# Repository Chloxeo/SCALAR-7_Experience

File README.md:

# SCALAR-7 : Carte Experience Bas

Experiment board of the **lower stage** of **SCALAR-7**, a two-stage rocket launched at **C'Space 2026**.
It measures the stage's flight parameters (accelerations, angular rates, attitude, pressure, altitude, temperature), tracks its position with GNSS, controls two onboard cameras and downlinks its data to the ground over LoRa.

---
## Table of contents

- [Board features](#board-features)
- [Architecture](#architecture)
  - [Power supply](#power-supply)
  - [Microcontroller](#microcontroller)
  - [Telemetry](#telemetry)
  - [Experiments](#experiments)
  - [HMI connection](#hmi-connection)
- [Main components](#main-components)
- [Repository structure](#repository-structure)

---

## Board features

| Function | Implementation |
|---|---|
| Processing / logging | Raspberry Pi **Pico** (RP2040) |
| Flight measurements | **WitMotion WT901B** inertial measurement unit: accelerometer, gyroscope, magnetometer, barometer, temperature (UART, I²C optional) |
| Positioning | **u-blox MAX-M10S** GNSS module (I²C, UART optional) |
| Ground link | **Microchip RN2483** LoRa 868 MHz module (UART), RF output split across two antennas |
| Video | Two JST connectors for the cameras (power, UART, control GPIOs) |
| Power supply | 2S battery, protected input (reverse polarity, overcurrent), 3.3 V and 5 V regulators |
| HMI interface | D-Sub 15 connector: power, jack, status LED, debug UART and SWD, camera control |
| Indicators | Power LED, GNSS PPS LED |

---

## Architecture

```mermaid
flowchart LR
    BAT[2S battery<br/>J5] --> IHM[HMI connector<br/>D-Sub 15]
    IHM -- VBATT_IHM --> PROT[Reverse-polarity P-MOS<br/>+ polyfuse]
    PROT --> REG33[LD1117 3V3]
    PROT --> REG5[L7805 5V]
    PROT --> CAM[Cameras 1 and 2]

    REG5 --> PICO[Raspberry Pi Pico]
    IHM -- ALIM_DEBUG --> PICO
    REG33 --> GPS[MAX-M10S<br/>GNSS]
    REG33 --> LORA[RN2483<br/>LoRa 868 MHz]
    REG5 --> IMU[WT901B<br/>IMU + barometer]

    GPS <-- I2C --> PICO
    LORA <-- UART --> PICO
    IMU <-- UART --> PICO
    CAM <-- UART / GPIO --> PICO
    LORA --> SPLIT[Power divider] --> ANT[2 antennas]
    IHM <-- UART / SWD / jack --> PICO
```

### Power supply

The board is powered by a **2S** battery. The supply goes through the HMI before coming back to the board, so the board can be switched on from the outside. The input is protected against reverse polarity (P-MOSFET) and overcurrent (polyfuse), then two linear regulators generate the **3V3** rail (GNSS, LoRa) and the **5V** rail (Pico, IMU). The cameras are powered directly from the protected battery line.

### Microcontroller

A **Raspberry Pi Pico** handles IMU and GNSS acquisition, camera control and LoRa frame transmission. It is mounted on two pin headers that also serve as test points. Its VSYS input is supplied either by the board's 5V rail or by the HMI debug supply through two diodes, so it can be programmed without the battery.

### Telemetry

- **GNSS**: a **u-blox MAX-M10S** module provides the position and a PPS signal. It connects to an external antenna and keeps its data in memory thanks to a backup battery.
- **LoRa**: an **RN2483** module (868 MHz, UART) sends the data to the ground. Its RF output is split across two antennas by a power divider.

### Experiments

- **Flight measurements**: **WT901B** inertial measurement unit, connected over UART. It provides accelerations, angular rates, attitude, pressure, altitude and temperature.
- **Video**: two cameras, powered by the board and controlled over UART and GPIO.

### HMI connection

The **D-Sub 15** connector links the board to the HMI. It carries the battery supply (out and back, for switching the board on), the jack, the status LED, the Pico's debug UART and SWD, and the camera control GPIOs.

---

## Main components

| Ref. | Component | Function |
|---|---|---|
| — | Raspberry Pi Pico | Microcontroller |
| U1 | u-blox MAX-M10S | GNSS receiver |
| U2 | Microchip RN2483 | LoRa 868 MHz module |
| U3 | PD0810J5050S2HF | RF power divider |
| W1 | WitMotion WT901B | IMU with barometer |
| IC2 | ST LD1117DT33TR | 3.3 V regulator |
| IC3 | ST L7805CDT-TR | 5 V regulator |
| Q2 | Vishay SQD50P04-13L | Reverse-polarity protection |
| F1 | Littelfuse 1812L260/16MR | Polyfuse |
| J2 | D-Sub 15 | HMI connection |
| J8, J9 | 5-pin connectors | Cameras |

---

## Repository structure

```
SCALAR-7_Carte_Experience_Bas/
├── hardware/          # KiCad project
├── images/
├── schematic.pdf
└── README.md
```

---

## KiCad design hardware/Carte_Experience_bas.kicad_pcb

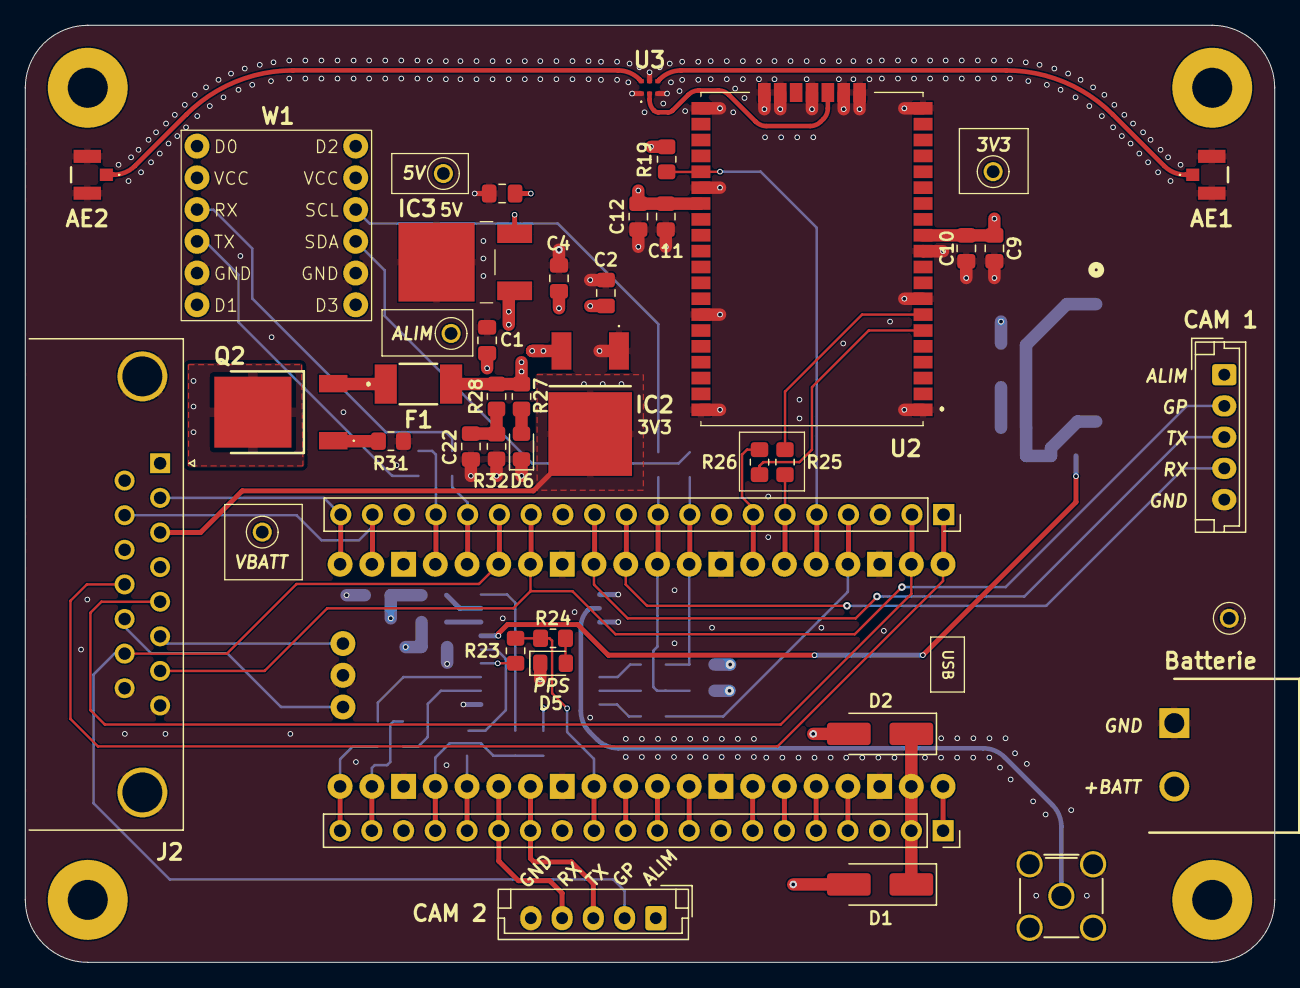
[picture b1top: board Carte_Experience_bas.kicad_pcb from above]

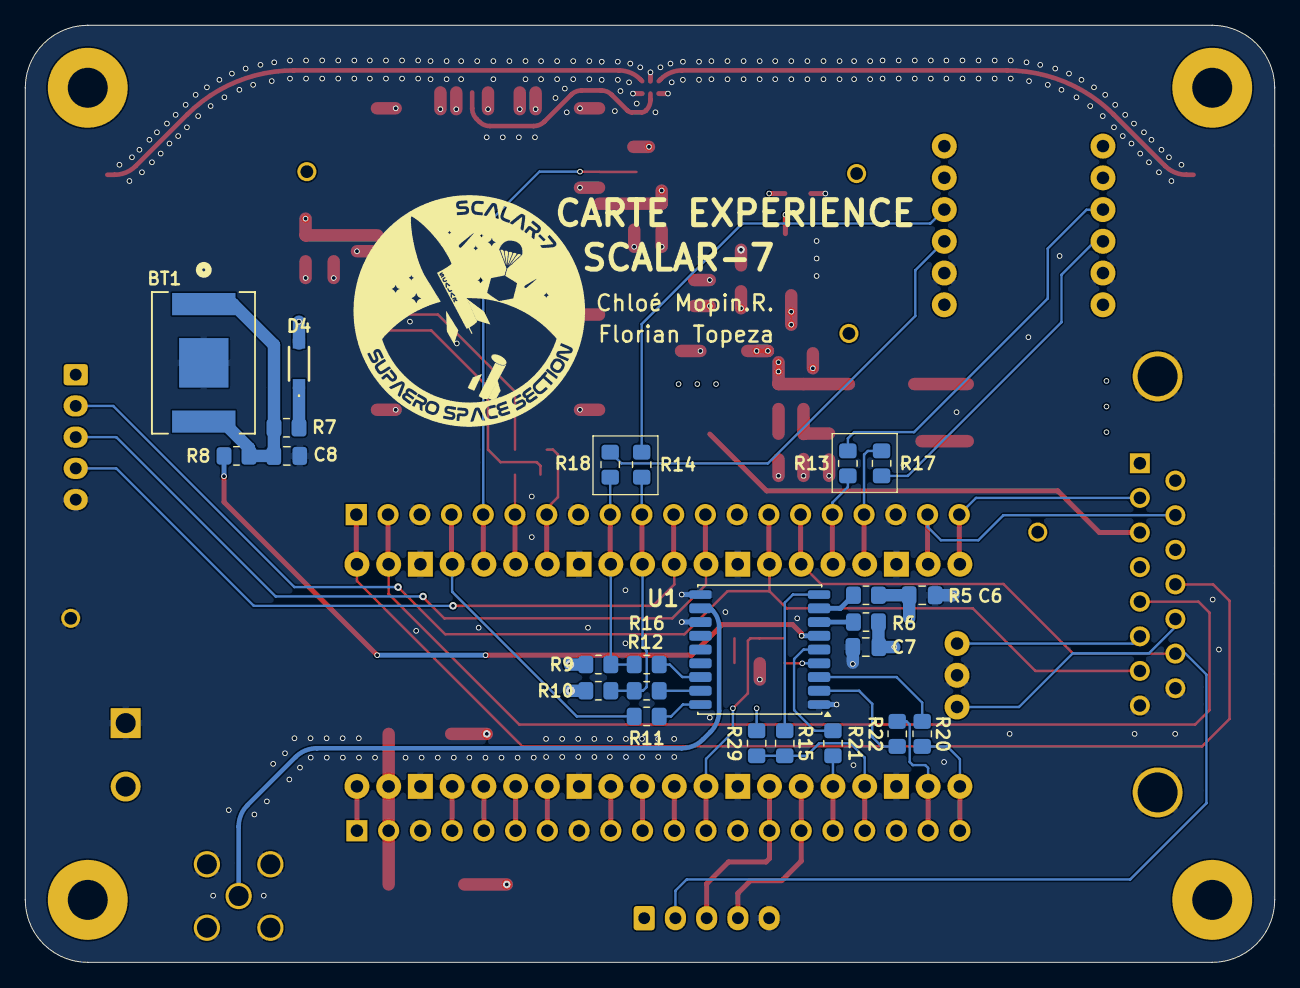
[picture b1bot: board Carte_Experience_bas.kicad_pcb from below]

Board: 4 copper layers, 100.0 x 75.0 mm, 72 parts (24 on the bottom side), 61 nets.

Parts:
AE1, AE2: Antenna_Shield; CONUFL001SMDT
AE3: Antenna_Shield; SMA_coude
BT1: 6.8mm 3.3V; pile btn
C1, C7, C8, C10, C11: 100nF; C_0805_2012Metric_Pad1.18x1.45mm_HandSolder
C2, C6: 10uF; C_0805_2012Metric_Pad1.18x1.45mm_HandSolder
C4: 0,33uF; C_0805_2012Metric_Pad1.18x1.45mm_HandSolder
C5: 0,1uF; C_0805_2012Metric_Pad1.18x1.45mm_HandSolder
C9, C12: 100uF; C_0805_2012Metric_Pad1.18x1.45mm_HandSolder
C22: 1uF; C_0805_2012Metric_Pad1.18x1.45mm_HandSolder
D1, D2: D; D_SMA_Handsoldering
D4: BAT54W
D5: LED_PPS; LED_0805_2012Metric_Pad1.15x1.40mm_HandSolder
D6: LED; LED_0805_2012Metric_Pad1.15x1.40mm_HandSolder
F1: 1812L260_16MR; 1812L010DR
H1, H2, H3, H4: MountingHole; MountingHole_3.2mm_M3_Pad
IC2: LD1117DT33TR
IC3: L7805CDT-TR; L7805CDTTR
J1: PICO
J2: DA15_Pins_MountingHoles; DSUB-15_Pins_Horizontal_P2.77x2.84mm_EdgePinOffset7.70mm_Ho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
J3: DEBUG_L; PinSocket_1x20_P2.54mm_Vertical
J4: DEBUG_R; PinSocket_1x20_P2.54mm_Vertical
J5: Batterie; OQ0254510000G
J8: CAM 1; JST_EH_B5B-EH-A_1x05_P2.50mm_Vertical
J9: CAM 2; JST_EH_B5B-EH-A_1x05_P2.50mm_Vertical
Q2: SQD50P04-13L_T4GE3; Q2 SQD50P0413L_T4GE3
R5, R6, R8, R11, R12, R13, R14, R15, R16, R17, R18, R20, R21, R22, R23, R25, R26: 0R; R_0805_2012Metric_Pad1.20x1.40mm_HandSolder
R7: 3.3k; R_0805_2012Metric_Pad1.20x1.40mm_HandSolder
R9, R10: 2.2k; R_0805_2012Metric_Pad1.20x1.40mm_HandSolder
R19, R28, R29: 10k; R_0805_2012Metric_Pad1.20x1.40mm_HandSolder
R24: 160R; R_0805_2012Metric_Pad1.20x1.40mm_HandSolder
R27: 400; R_0805_2012Metric_Pad1.20x1.40mm_HandSolder
R31: 0; R_0805_2012Metric_Pad1.20x1.40mm_HandSolder
R32: 2k; R_0805_2012Metric_Pad1.20x1.40mm_HandSolder
TP1: ALIM; 5003
TP2: REG; 5003
TP3: 3V3; 5003
TP4: 5V; 5003
TP5: GND; 5003
U1: MAX-M10S; ublox_MAX
U2: LoRa RN2483; RN2483AIRM104
U3: PD0810J5050S2HF
W1: WT901B; TestPoint_Pad_1.0x1.0mm

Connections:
+3.3V: C2.1, C6.1, C7.1, C9.1, C10.1, C11.1, C12.1, D4.2 (A), IC2.2 (OUT), J2.3, R5.1, R6.1, R9.1, R10.1, R19.1, R29.1, TP3.TP, U2.12 (VDD), U2.34 (VDD)
+5V: C5.1, D2.2 (A), IC3.3 (OUT), J2.11 (P111), TP4.TP, W1.2 (VCC), W1.8 (VCC)
+BATT: J2.1, J5.2, TP1.TP
ALIM_CAM: C1.1, C4.1, F1.2, IC2.3 (IN), IC3.1 (IN), J8.1, J9.1, R27.1, R28.1, TP2.TP
ALIM_DEBUG: D1.2 (A), J2.4
BACKUP_GPS: BT1.1 (+), C8.1, R7.2, R8.1
EXTINT_GPS: J1.25 (GP19), J4.16, R21.1
GND: AE1.2 (GND), AE1.3 (GND), AE2.2 (GND), AE2.3 (GND), AE3.2 (GND), AE3.3 (GND), AE3.4 (GND), AE3.5 (GND), BT1.2 (-), C1.2, C2.2, C4.2, C5.2, C6.2, C7.2, C8.2, C9.2, C10.2, C11.2, C12.2, C22.2, D5.1 (K), D6.1 (K), IC2.1 (GND), IC3.2 (GND), J1.3 (GND_1), J1.8 (GND_2), J1.13 (GND_3), J1.18 (GND_4), J1.23 (GND_5), J1.28 (GND_6), J1.33 (GND_7), J1.38 (GND_8), J1.D2 (GND_9), J2.0 (PAD), J2.8, J2.15, J3.3, J3.8, J3.13, J3.18, J4.3, J4.8, J4.13, J4.18, J5.1, J8.5, J9.5, R31.2, R32.2, TP5.TP, U1.1 (GND), U1.10 (GND), U1.12 (GND), U2.1 (GND), U2.8 (GND), U2.11 (GND), U2.20 (GND), U2.21 (GND), U2.22 (GND), U2.24 (GND), U2.26 (GND), U2.27 (GND), U2.28 (GND), U2.33 (GND), U2.41 (GND), U2.47 (GND), U3.1 (GND_1), U3.3 (GND_2), U3.5 (GND_3), W1.5 (GND), W1.11 (GND)
GP_CAM1: J1.14 (GP10), J2.7, J3.14, J8.2
GP_CAM2: J1.15 (GP11), J2.14, J3.15, J9.2
JACK_IHM: J1.19 (GP14), J2.10, J3.19
LED_ETAT: J1.20 (GP15), J2.2, J3.20
unnamed: AE1.1 (A), U3.4 (OUTPUT_1)
unnamed: AE2.1 (A), U3.6 (OUTPUT_2)
unnamed: AE3.1 (A), U1.11 (RF_IN)
unnamed: C22.1, R28.2, R32.1
unnamed: D1.1 (K), D2.1 (K), J1.39 (VSYS), J4.2
unnamed: D4.1 (K), R7.1
unnamed: D5.2 (A), R24.1
unnamed: D6.2 (A), R27.2
unnamed: Q2.1 (G), R31.1
unnamed: F1.1, Q2.3 (S)
unnamed: R21.2, U1.5 (EXTINT)
unnamed: R20.2, U1.3 (RXD)
unnamed: R12.2, U1.17 (SCL)
unnamed: R16.2, U1.16 (SDA)
unnamed: R23.2, U1.4 (TIMEPULSE)
unnamed: R22.2, U1.2 (TXD)
unnamed: R5.2, U1.8 (VCC)
unnamed: R6.2, U1.7 (VCC_IO)
unnamed: R8.2, U1.6 (V_BCKP)
unnamed: R15.2, U1.9 (~RESET)
unnamed: R11.2, U1.18 (~SAFEBOOT)
unnamed: R25.2, U2.7 (UART_RX)
unnamed: R26.2, U2.6 (UART_TX)
unnamed: R13.2, W1.3 (RX)
unnamed: R14.2, W1.9 (SCL)
unnamed: R18.2, W1.10 (SDA)
unnamed: R17.2, W1.4 (TX)
PPS_GPS: J1.29 (GP22), J4.12, R23.1, R24.2
RFH: U2.23 (RFH), U3.2 (INPUT)
RX_CAM1: J1.11 (GP8), J3.11, J8.4
RX_CAM2: J1.26 (GP20), J4.15, J9.4
RX_DEBUG: J1.2 (GP1), J2.5, J3.2
RX_GPS: J1.21 (GP16), J4.20, R20.1
RX_LORA: J1.6 (GP4), J3.6, R25.1
RX_WT: J1.16 (GP12), J3.16, R13.1
SCL: J1.10 (GP7), J3.10, R10.2, R12.1, R14.1
SDA: J1.9 (GP6), J3.9, R9.2, R16.1, R18.1
SWCLK_DEBUG: J1.D1 (SWCLK), J2.13
SWDIO_DEBUG: J1.D3 (SWDIO), J2.6
TX_CAM1: J1.12 (GP9), J3.12, J8.3
TX_CAM2: J1.27 (GP21), J4.14, J9.3
TX_DEBUG: J1.1 (GP0), J2.12, J3.1
TX_GPS: J1.22 (GP17), J4.19, R22.1
TX_LORA: J1.7 (GP5), J3.7, R26.1
TX_WT: J1.17 (GP13), J3.17, R17.1
VBATT_IHM: J2.9, Q2.2 (D)
~RESET_GPS: J1.24 (GP18), J4.17, R15.1, R29.2
~RESET_LORA: J1.5 (GP3), J3.5, R19.2, U2.32 (~RESET)
~SAFEBOOT_GPS: J1.4 (GP2), J3.4, R11.1
